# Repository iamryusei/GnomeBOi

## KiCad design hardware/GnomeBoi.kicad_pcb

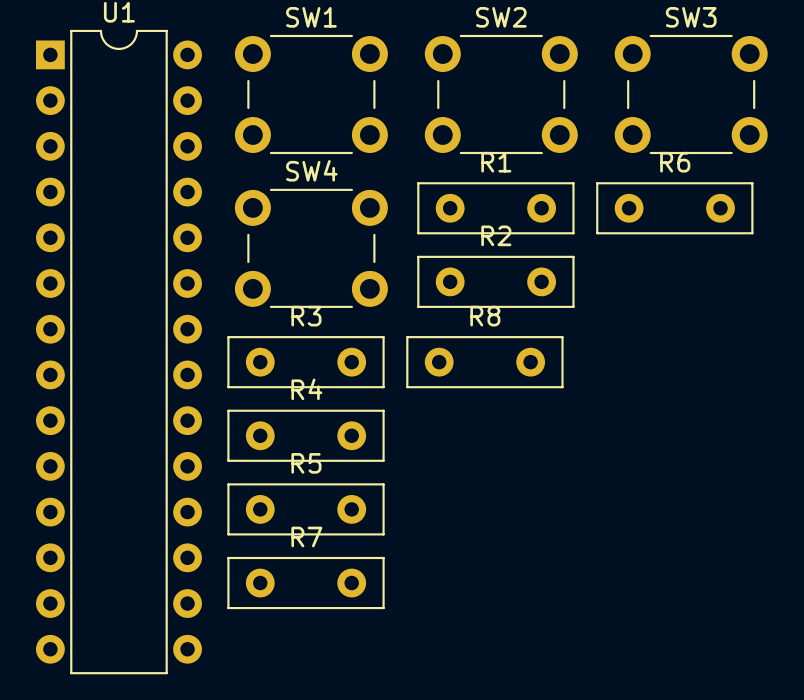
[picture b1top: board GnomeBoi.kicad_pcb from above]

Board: 2 copper layers, 13 parts (0 on the bottom side), 10 nets, no tracks yet.

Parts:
R1, R2, R3, R4, R5, R6, R7, R8: R_Small_US; R_Box_L8.4mm_W2.5mm_P5.08mm
SW1, SW2, SW3, SW4: SW_Push_Dual_x2; SW_PUSH_6mm_H4.3mm
U1: ATmega328P-PU; DIP-28_W7.62mm

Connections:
unnamed: R1.1, U1.23
unnamed: R1.2, R2.2, R3.2, R4.2, R5.2, R6.2, R7.2, R8.2, U1.8, U1.22
unnamed: R2.1, SW1.1, U1.24
unnamed: R3.1, SW2.1, U1.25
unnamed: R4.1, U1.26
unnamed: R5.1, SW3.1, U1.6
unnamed: R6.1, U1.11
unnamed: R7.1, SW4.1, U1.12
unnamed: R8.1, U1.13
unnamed: SW1.2, SW2.2, SW3.2, SW4.2, U1.7

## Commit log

2020-10-13 added some source code and hardware schematics
2020-10-14 reorganized pin definition header "src/Firmware/Private/config.h"
